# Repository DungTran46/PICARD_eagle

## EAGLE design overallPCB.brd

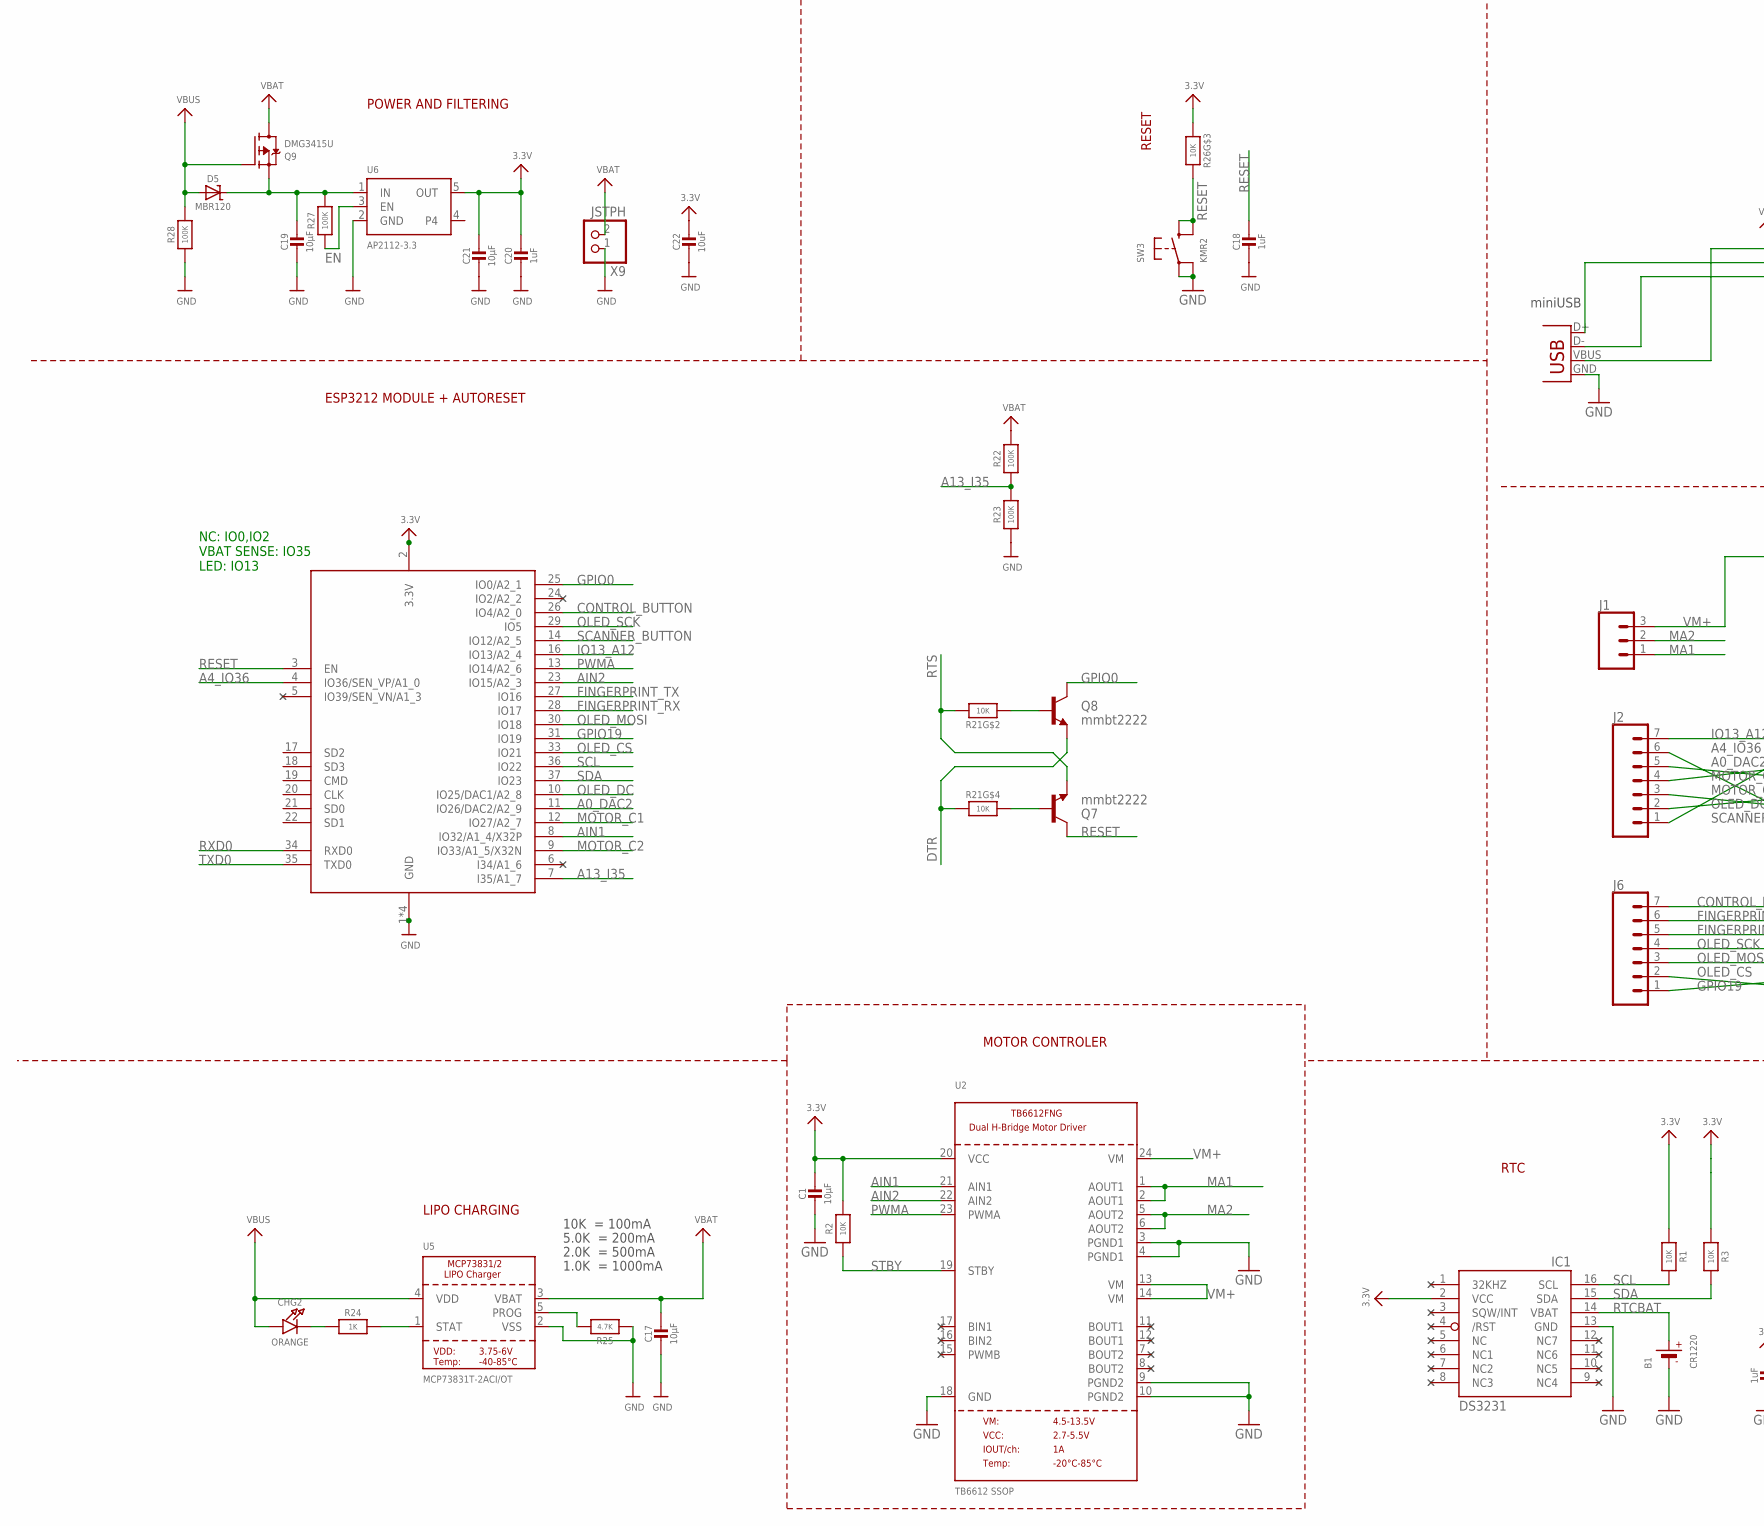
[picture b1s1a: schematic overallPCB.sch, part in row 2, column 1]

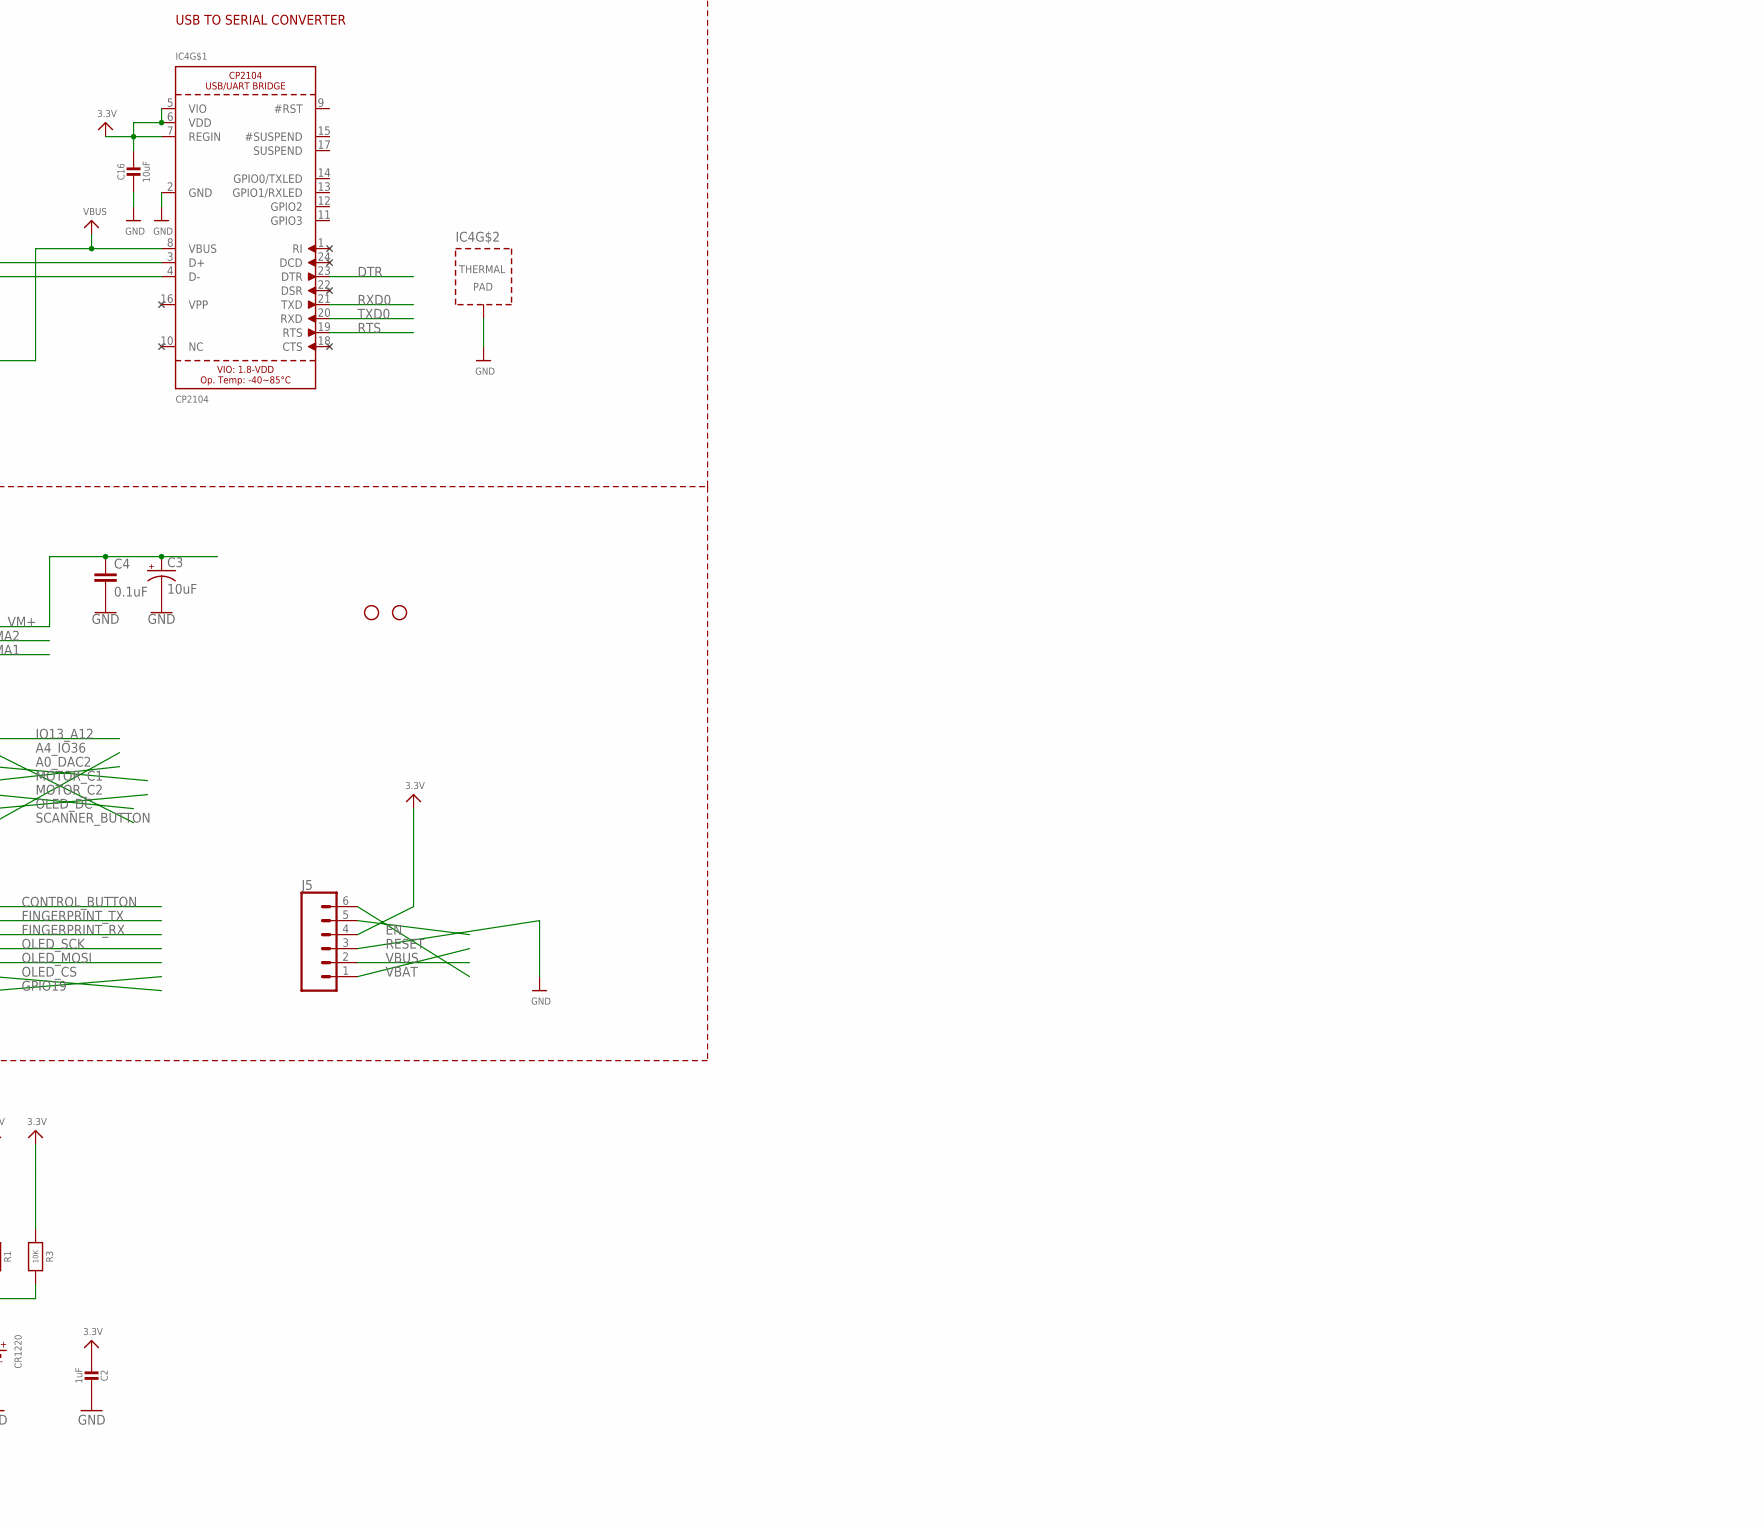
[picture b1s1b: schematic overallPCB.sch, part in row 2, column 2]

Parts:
B1: CR1220
C1, C17, C19, C21: 10µF; 0805-NO
C2: 1uF; 0805-NO
C3: 10uF; EIA3216
C4: 0.1uF; 0402
C16, C22: 10uF; 0805-NO
C18, C20: 1uF; 0603-NO
CHG2: ORANGE; CHIPLED_0805_NOOUTLINE
D5: MBR120; SOD-123
H1, H2: STAND-OFF
IC1: DS3231/SO; SO16W
IC4: CP2104; QFN24_4MM_SMSC
J1: CONN_031X03_NO_SILK; 1X03_NO_SILK
J2, J6: CONN_07NO_SILK; 1X07_NO_SILK
J5: CONN_06NO_SILK_FEMALE_PTH; 1X06_NO_SILK
Q7, Q8: mmbt2222; SOT23-3
Q9: DMG3415U; SOT23-R
R1, R2, R3: 10K; 0805-NO
R21, R26: 10K; RESPACK_4X0603
R22, R23, R27, R28: 100K; 0603-NO
R24: 1K; 0603-NO
R25: 4.7K; 0603-NO
SW3: KMR2; BTN_KMR2_4.6X2.8
U2: TB6612 SSOP; SSOP24
U5: MCP73831T-2ACI/OT; SOT23-5
U6: AP2112-3.3; SOT23-5
X1: Micro USB; USB-MINIB
X7: ESP32_WROOM32_SKINNY; WROOM32_SKINNY
X9: JSTPH; JSTPH2

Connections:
3.3V: C1.1, C2.2, C16.1, C20.1, C21.1, C22.1, IC1.2 (VCC), IC4.5 (VIO), IC4.6 (VDD), IC4.7 (REGIN), J5.4, R1.1, R2.2, R3.1, R26.3 (1), U2.20 (VCC), U6.5 (OUT), X7.2 (3.3V)
A0_DAC2: J2.4, X7.11 (IO26/DAC2/A2_9)
A4_IO36: J2.1, X7.4 (IO36/SEN_VP/A1_0)
A13_I35: R22.1, R23.2, X7.7 (I35/A1_7)
AIN1: U2.21 (AIN1), X7.8 (IO32/A1_4/X32P)
AIN2: U2.22 (AIN2), X7.23 (IO15/A2_3)
CONTROL_BUTTON: J6.7, X7.26 (IO4/A2_0)
DTR: IC4.23 (DTR), Q8.2 (E), R21.4 (1)
EN: J5.5, R27.1, U6.3 (EN)
FINGERPRINT_RX: J6.5, X7.28 (IO17)
FINGERPRINT_TX: J6.6, X7.27 (IO16)
GND: B1.-, C1.2, C2.1, C3.-, C4.2, C16.2, C17.2, C18.2, C19.2, C20.2, C21.2, C22.2, IC1.13 (GND), IC4.2 (GND), IC4.THERM (TP), J5.3, R23.1, R25.1, R28.1, SW3.A, SW3.A' (P1), U2.3 (PGND1), U2.4 (PGND1), U2.9 (PGND2), U2.10 (PGND2), U2.18 (GND), U5.2 (VSS), U6.2 (GND), X1.GND, X7.1 (GND), X7.15 (GND), X7.38 (GND), X7.P$1 (GND), X9.1
GPIO0: Q8.3 (C), X7.25 (IO0/A2_1)
GPIO19: J6.2, X7.31 (IO19)
IO13_A12: J2.7, X7.16 (IO13/A2_4)
MA1: J1.1, U2.1 (AOUT1), U2.2 (AOUT1)
MA2: J1.2, U2.5 (AOUT2), U2.6 (AOUT2)
MOTOR_C1: J2.5, X7.12 (IO27/A2_7)
MOTOR_C2: J2.2, X7.9 (IO33/A1_5/X32N)
unnamed: Q7.1 (B), R21.5 (2)
unnamed: Q8.1 (B), R21.2 (1)
unnamed: IC4.3 (D+), X1.D+
unnamed: IC4.4 (D-), X1.D-
unnamed: CHG2.C, R24.1
unnamed: R24.2, U5.1 (STAT)
unnamed: R25.2, U5.5 (PROG)
unnamed: C19.1, D5.C, Q9.2 (S), R27.2, U6.1 (IN)
OLED_CS: J6.1, X7.33 (IO21)
OLED_DC: J2.3, X7.10 (IO25/DAC1/A2_8)
OLED_MOSI: J6.3, X7.30 (IO18)
OLED_SCK: J6.4, X7.29 (IO5)
PWMA: U2.23 (PWMA), X7.13 (IO14/A2_6)
RESET: C18.1, J5.1, Q7.3 (C), R26.6 (2), SW3.B (S), SW3.B' (S1), X7.3 (EN)
RTCBAT: B1.+$1 (+), IC1.14 (VBAT)
RTS: IC4.19 (RTS), Q7.2 (E), R21.7 (2)
RXD0: IC4.21 (TXD), X7.34 (RXD0)
SCANNER_BUTTON: J2.6, X7.14 (IO12/A2_5)
SCL: IC1.16 (SCL), R1.2, X7.36 (IO22)
SDA: IC1.15 (SDA), R3.2, X7.37 (IO23)
STBY: R2.1, U2.19 (STBY)
TXD0: IC4.20 (RXD), X7.35 (TXD0)
VBAT: C17.1, J5.6, Q9.3 (D), R22.2, U5.3 (VBAT), X9.2
VBUS: CHG2.A, D5.A, IC4.8 (VBUS), J5.2, Q9.1 (G), R28.2, U5.4 (VDD), X1.VBUS
VM+: C3.+, C4.1, J1.3, U2.13 (VM), U2.14 (VM), U2.24 (VM)

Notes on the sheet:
POWER AND FILTERING
USB TO SERIAL CONVERTER
RESET
10K = 100mA
5.0K = 200mA
2.0K = 500mA
1.0K = 1000mA
LIPO CHARGING
ESP3212 MODULE + AUTORESET
NC: IO0,IO2 VBAT SENSE: IO35 LED: IO13
RTC
MOTOR CONTROLER
miniUSB

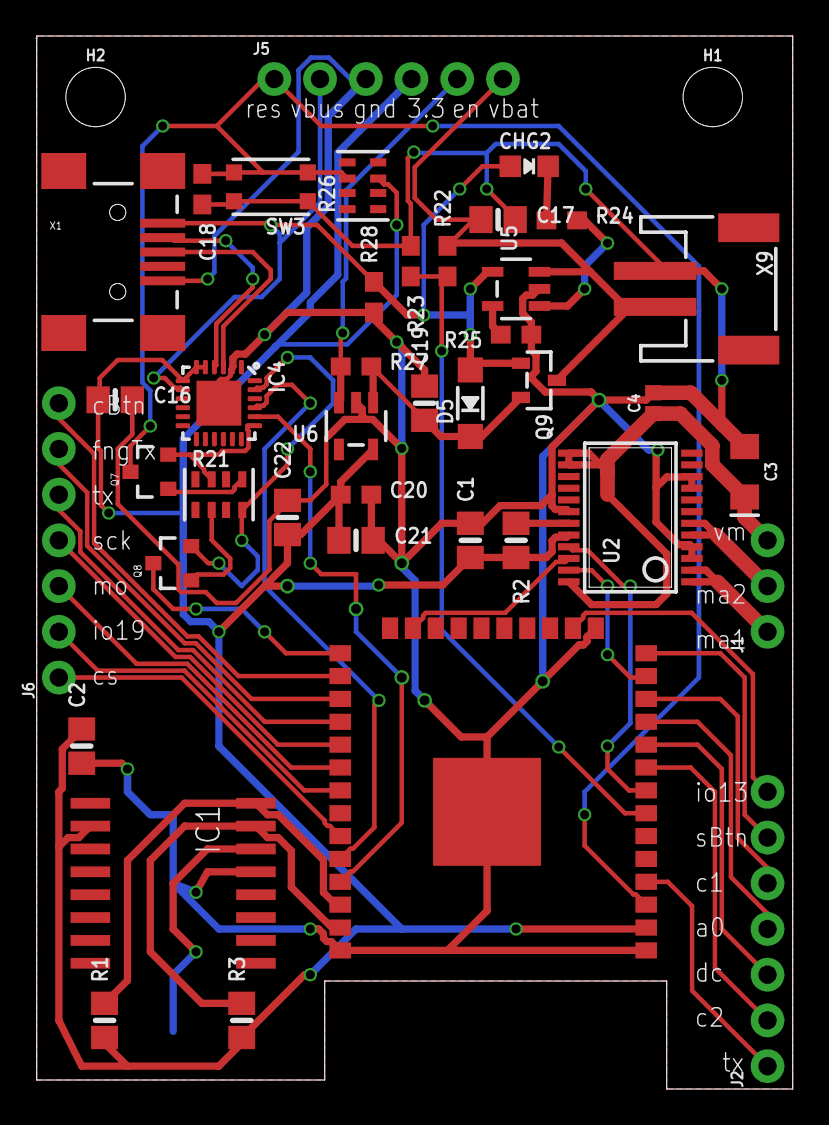
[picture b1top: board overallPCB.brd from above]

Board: 2 copper layers, 42.0 x 58.5 mm, 43 parts (1 on the bottom side), 44 nets.

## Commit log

2018-04-25 Add RTC; ESP32 Feather
2018-05-02 TB6612 motor controller/hbridge
2018-05-02 update overallPCB

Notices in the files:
parts and their libraries:
microbuilder: This work is placed in the public domain, and may be freely used for commercial and non-commercial work with the following conditions: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
SparkFun-Capacitors: Licensing: Creative Commons ShareAlike 4.0 International - https://creativecommons.org/licenses/by-sa/4.0
